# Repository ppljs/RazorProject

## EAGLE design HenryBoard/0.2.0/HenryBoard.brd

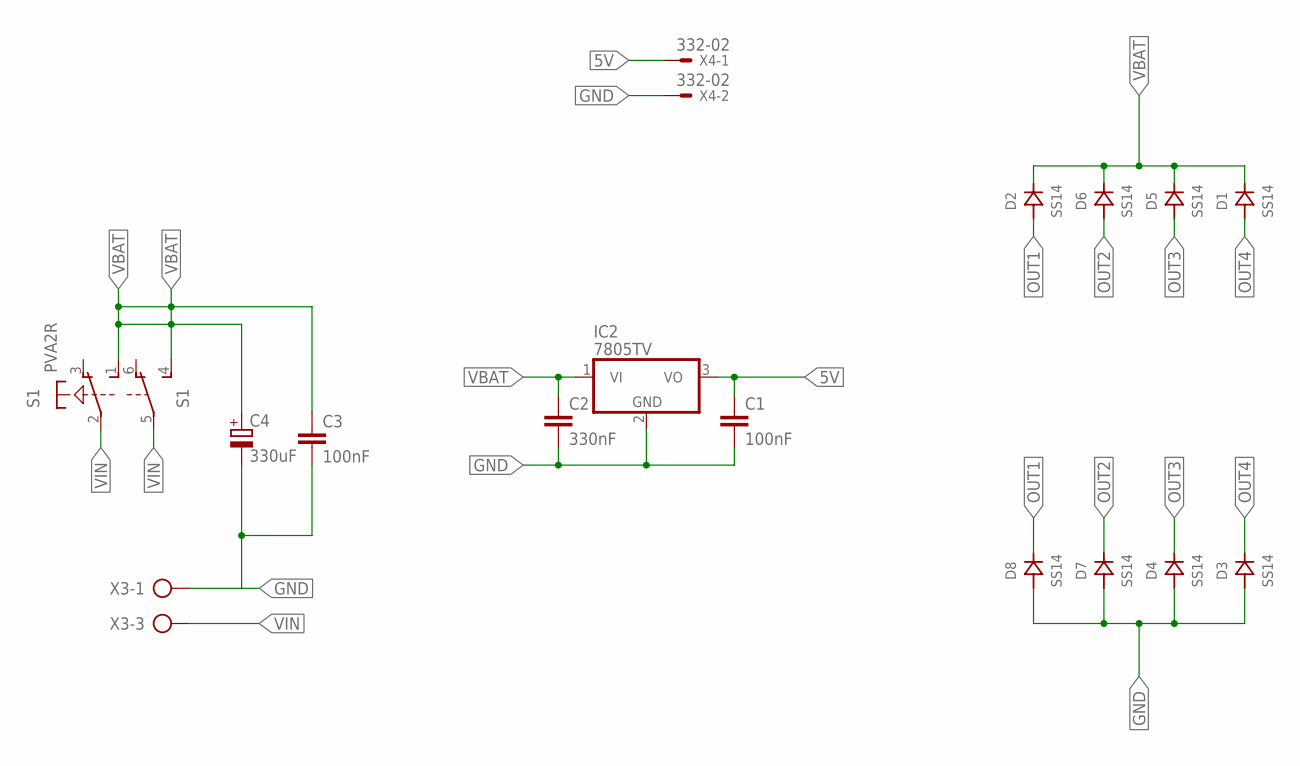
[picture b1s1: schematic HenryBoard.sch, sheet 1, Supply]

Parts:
C1, C3: 100nF; 0805
C2: 330nF; C025-030X050
C4: 330uF; E5-13
D1, D2, D3, D4, D5, D6, D7, D8: SS14; DO214
IC2: 7805TV; TO220V
S1: PVA2R
X3: AK300/3
X4: 332-02

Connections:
5V: C1.1, IC2.3 (VO); also elsewhere on the board
GND: C1.2, C2.2, C3.2, C4.-, D3.ANODE, D4.ANODE, D7.ANODE, D8.ANODE, IC2.2 (GND), X3.1; also elsewhere on the board
OUT1: D2.ANODE, D8.CATHODE; also elsewhere on the board
OUT2: D6.ANODE, D7.CATHODE; also elsewhere on the board
OUT3: D4.CATHODE, D5.ANODE; also elsewhere on the board
OUT4: D1.ANODE, D3.CATHODE; also elsewhere on the board
VBAT: C2.1, C3.1, C4.+, D1.CATHODE, D2.CATHODE, D5.CATHODE, D6.CATHODE, IC2.1 (VI), S1.1 (S), S1.4 (S); also elsewhere on the board
VIN: S1.2, S1.5, X3.3

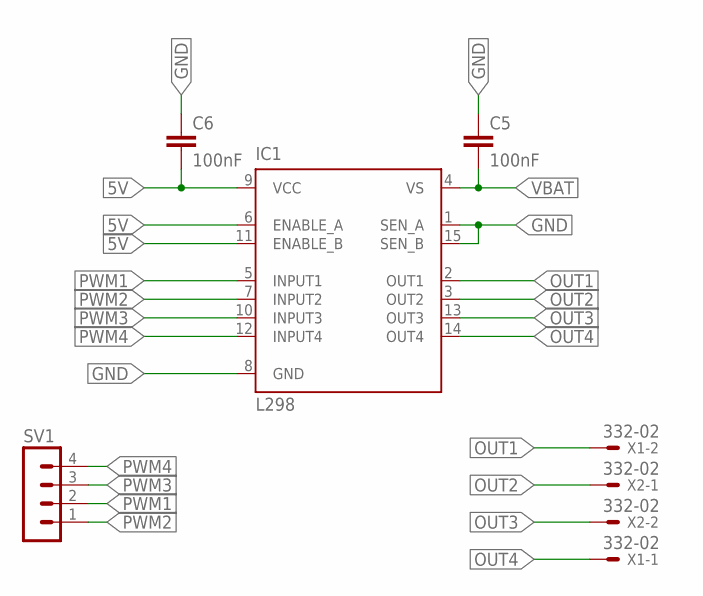
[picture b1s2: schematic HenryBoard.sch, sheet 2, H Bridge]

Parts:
C5, C6: 100nF; 0805
IC1: L298; MULTIWATT-15
SV1: MA04-1
X1, X2: 332-02

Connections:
5V: C6.2, IC1.6 (ENABLE_A), IC1.9 (VCC), IC1.11 (ENABLE_B); also elsewhere on the board
GND: C5.1, C6.1, IC1.1 (SEN_A), IC1.8 (GND), IC1.15 (SEN_B); also elsewhere on the board
OUT1: IC1.2 (OUT1), X1.2; also elsewhere on the board
OUT2: IC1.3 (OUT2), X2.1; also elsewhere on the board
OUT3: IC1.13 (OUT3), X2.2; also elsewhere on the board
OUT4: IC1.14 (OUT4), X1.1; also elsewhere on the board
PWM1: IC1.5 (INPUT1), SV1.2
PWM2: IC1.7 (INPUT2), SV1.1
PWM3: IC1.10 (INPUT3), SV1.3
PWM4: IC1.12 (INPUT4), SV1.4
VBAT: C5.2, IC1.4 (VS); also elsewhere on the board

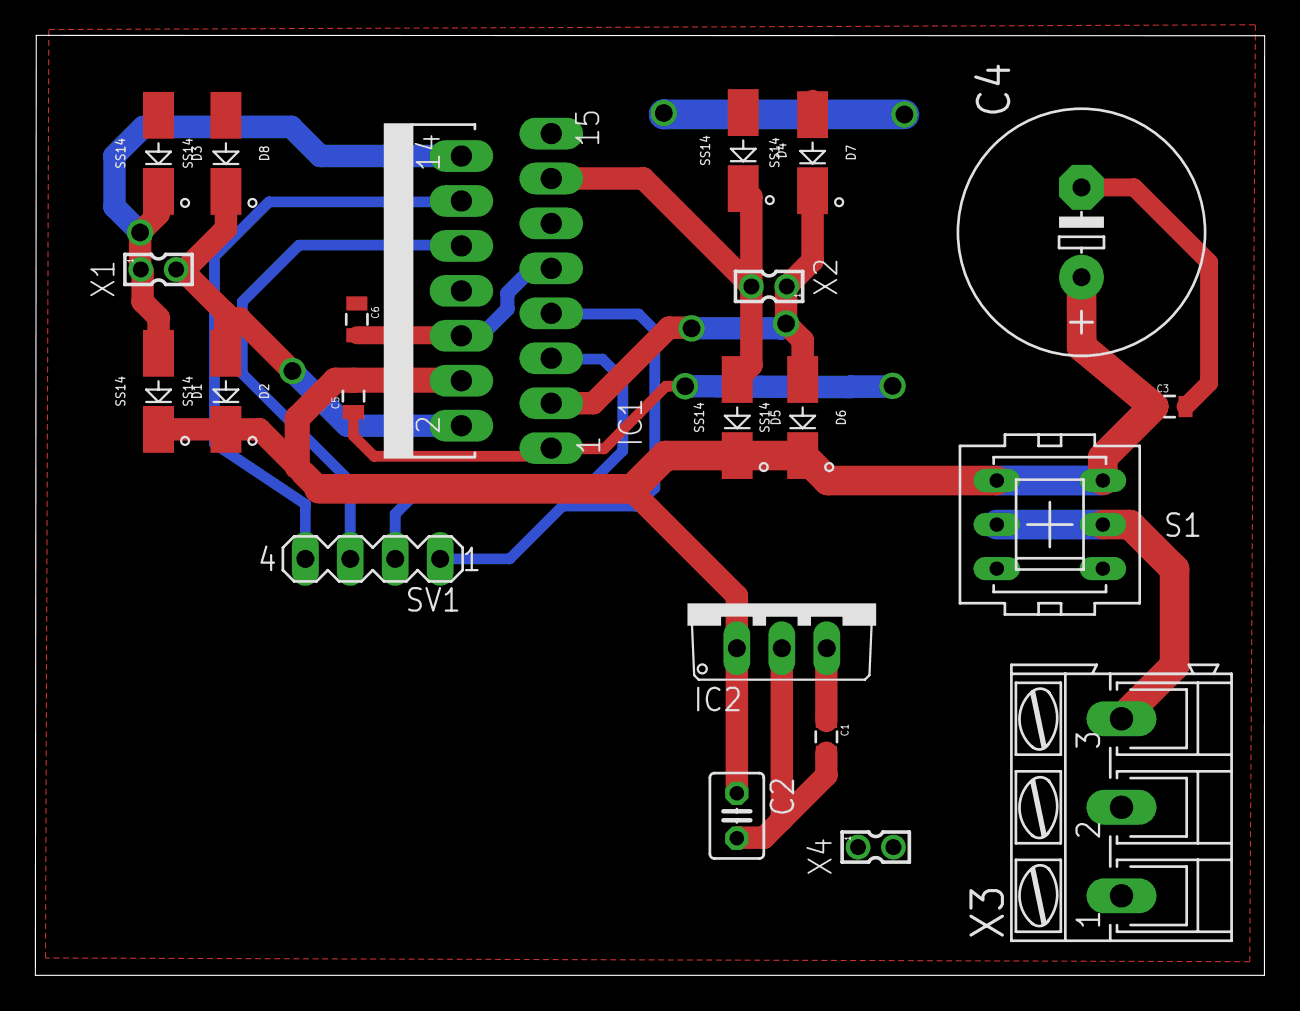
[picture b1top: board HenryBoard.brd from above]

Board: 2 copper layers, 69.5 x 53.1 mm, 22 parts (0 on the bottom side), 12 nets.

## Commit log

2017-08-29 Adding first openCV 3.3 test (not working)
2017-08-29 Adiciona HenryBoard
    HenryBoard adicionada ao projeto em sua versão 0.2.0, ainda em processo de revisão.
2017-08-29 Correcting linking flags for OpenCV
2017-08-30 Creating 'BallTrack' class (to be renamed) already reading images from webcam and transforming them to HSV space
2017-08-30 Added vision code
2017-09-01 Added the SolidWorks's files
2017-09-02 Added tracking functionality for my orange fruit
2017-09-02 Adding atrocious upper limit for object area
2017-09-02 Refactoring project folders
2017-09-09 modified the body and created the 'mancais'
2017-09-15 Testando ReactiveX (Não deve funcionar com OpenCV, pois bool VideoCapture::read(Mat) não retorna a matriz lida)
2017-09-15 changes to carapace and teto
2017-09-16 Changing project to QT
2017-09-16 Adding multithreading support [perhaps]
2017-09-17 Adding debug prints
2017-09-21 vision working with multiple objs
2017-09-22 early stage of the vision and decision making
2017-09-22 ready to test
2017-09-23 correction of the pwm mistake
2017-09-23 optimization
2017-09-23 to merge
2017-09-23 merge
2017-09-23 another optimiztion

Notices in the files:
parts and their libraries:
SparkFun-Capacitors: Licensing: Creative Commons ShareAlike 4.0 International - https://creativecommons.org/licenses/by-sa/4.0
